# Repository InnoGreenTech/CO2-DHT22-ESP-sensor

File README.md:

CO2-DHT22-ESP-sensor
====================

Description:
------------

This is a MH-Z19B, CO2 sensor, a DHT22, humidity and temperature sensor; connected at a nodemcu with a oled screen.

It have a interface web and an update by http interface. It is possible to connect it in Modbus.

[*You can found more information on my web site on this page*](http://innogreentech.fr/en/connected-objects/measures/62-co2-temperature-and-humidity-sensor)

I share also the drawing, the pcb, and the box designe in this repository.

Contributing:
-------------

Fork it
Create your feature branch (git checkout -b my-new-feature)
Commit your changes (git commit -am 'Add some feature')
Push to the branch (git push origin my-new-feature)
Create new Pull Request

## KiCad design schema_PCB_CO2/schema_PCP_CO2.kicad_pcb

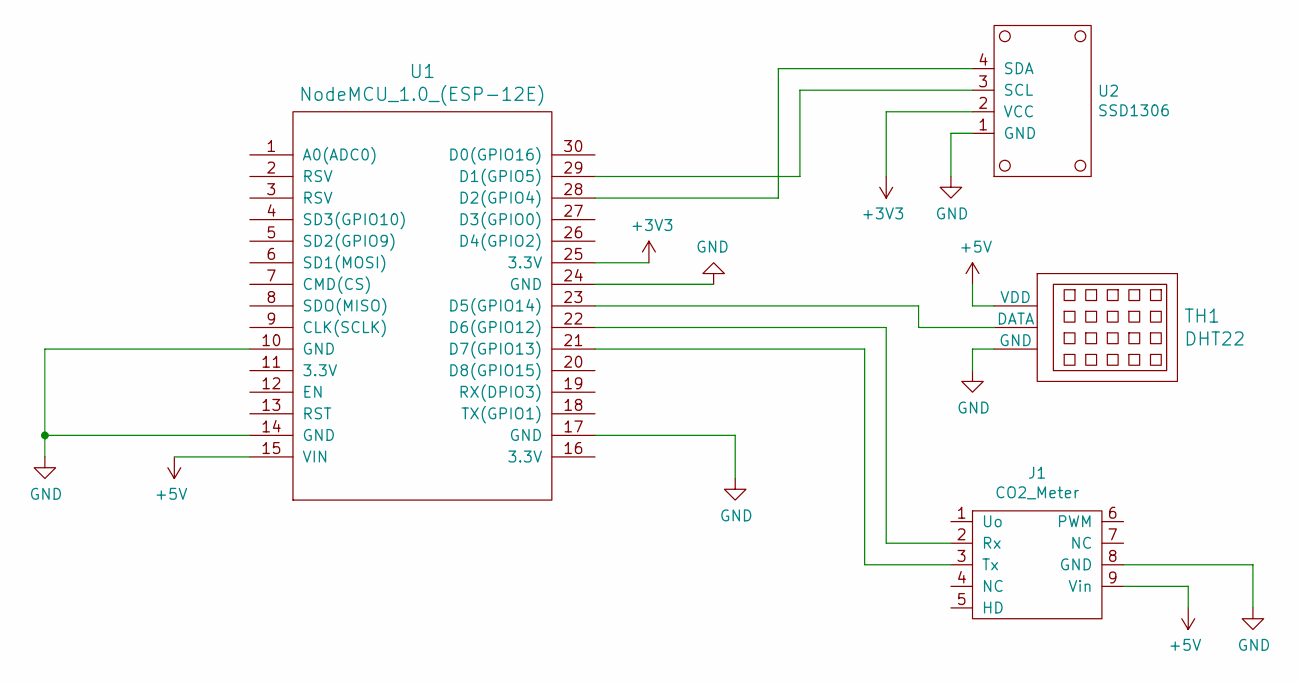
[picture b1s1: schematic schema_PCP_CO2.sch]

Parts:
J1: CO2_Meter; MHZ19B
TH1: DHT22; DHT22_Temperature_Humidity
U1: NodeMCU_1.0_(ESP-12E); NodeMCU-LoLinV3
U2: SSD1306

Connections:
+3V3: U1.25 (3.3V), U2.2 (VCC)
+5V: J1.9 (Vin), TH1.1 (VDD), U1.15 (VIN)
GND: J1.8 (GND), TH1.3 (GND), U1.10 (GND), U1.14 (GND), U1.17 (GND), U1.24 (GND), U2.1 (GND)
unnamed: J1.2 (Rx), U1.22 (D6(GPIO12))
unnamed: J1.3 (Tx), U1.21 (D7(GPIO13))
unnamed: TH1.2 (DATA), U1.23 (D5(GPIO14))
unnamed: U1.28 (D2(GPIO4)), U2.4 (SDA)
unnamed: U1.29 (D1(GPIO5)), U2.3 (SCL)

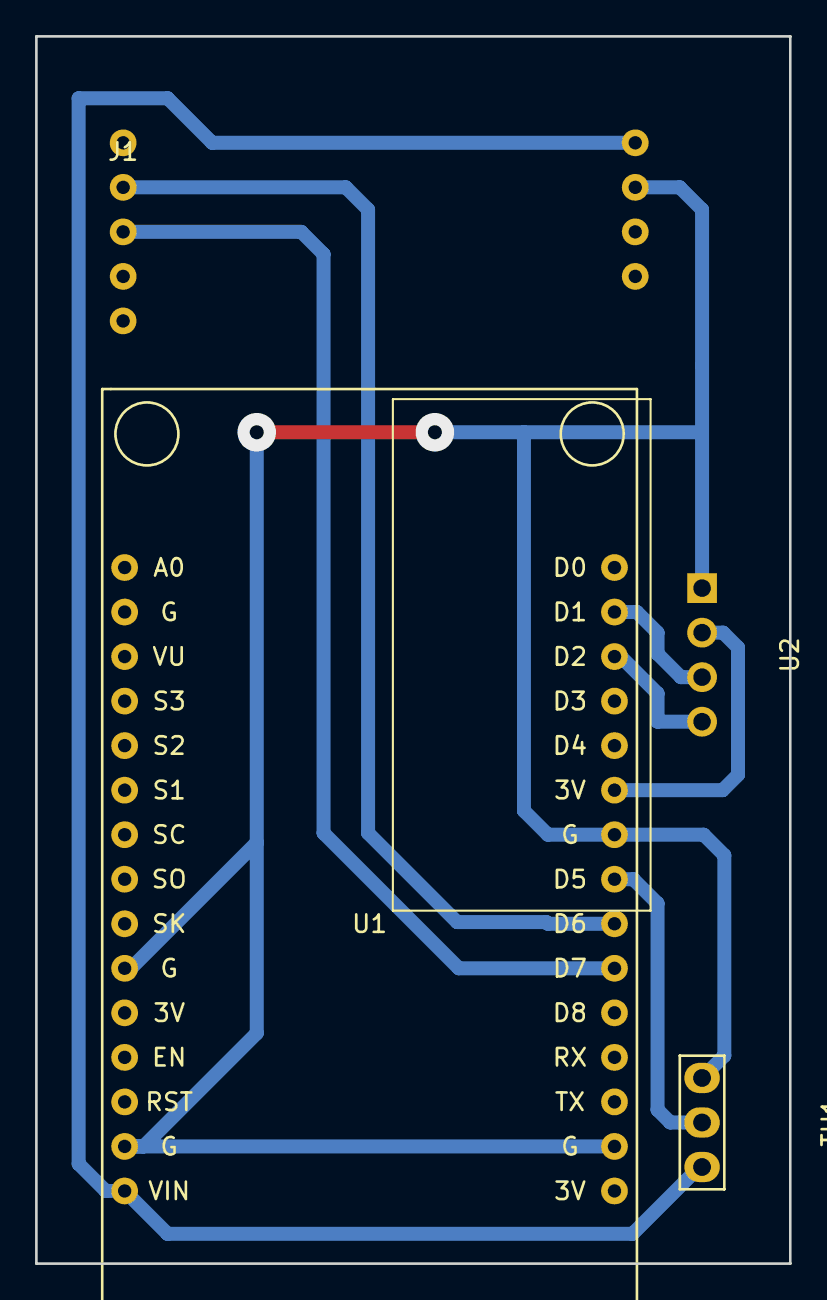
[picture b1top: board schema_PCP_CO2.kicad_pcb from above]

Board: 2 copper layers, 43.0 x 70.0 mm, 4 parts (0 on the bottom side), 8 nets.

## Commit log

2020-01-27 Put files
2020-01-29 modifiy Read file
2020-02-13 put good code
2020-02-13 update information in readme file
2020-04-29 improve serial communication and change web page
